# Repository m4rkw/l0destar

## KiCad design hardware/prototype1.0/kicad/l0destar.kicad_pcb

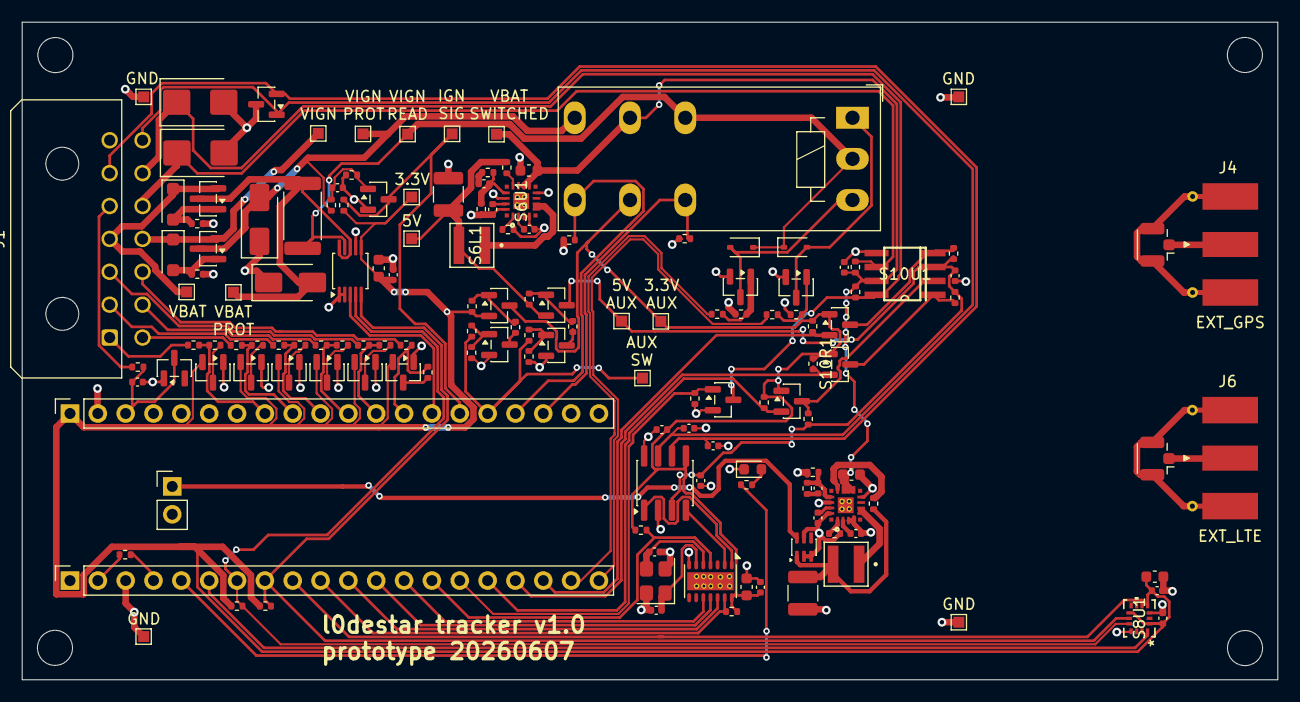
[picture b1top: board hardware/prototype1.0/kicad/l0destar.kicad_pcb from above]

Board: 2 copper layers, 114.5 x 60.0 mm, 153 parts (0 on the bottom side), 101 nets.

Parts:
DS10D2: SMBJ24A; D_SMB
H1, H2, H3, H4: MountingHole; MountingHole_3.2mm_M3
J1: Main connector; Molex_Micro-Fit_3.0_43045-1400_2x07_P3.00mm_Horizontal
J2: Conn_01x20_Socket; PinSocket_1x20_P2.54mm_Vertical
J3: Conn_01x20_Socket_21-40; PinSocket_1x20_P2.54mm_Vertical_21-40
J4: EXT_GPS; SMA_Molex_73251-1153_EdgeMount_Horizontal
J5: INT_GPS; U.FL_Hirose_U.FL-R-SMT-1_Vertical
J6: EXT_LTE; SMA_Molex_73251-1153_EdgeMount_Horizontal
J7: INT_LTE; U.FL_Hirose_U.FL-R-SMT-1_Vertical
J8: Conn_01x02_Pin; PinHeader_1x02_P2.54mm_Vertical
S1C1, S3C2, S4C1, S8C1, S8C3, S9C1, S9C2, S9C5, S10C1, S10C2: 100nF; C_0402_1005Metric
S1D1: BZX84C3V3; SOT-23
S1R1, S13R1: 1K; R_0402_1005Metric
S1R2, S1R3: 4.7K; R_0402_1005Metric
S1R4, S4R2, S5R1, S5R4, S6R4, S6R8, S7R2, S7R4, S7R6, S7R8, S11R1, S11R3, S11R5, S11R7, S11R9, S11R11: 100K; R_0402_1005Metric
S2D1, S2D3: BZT52C15; D_SOD-123F
S2D2, S2D4: SMAJ24A; D_SMA
S2Q1, S2Q2, S7Q2, S7Q4: SI2301CDS-T1-GE3; SOT-23
S2R1, S2R2, S5R2, S5R3, S5R5, S5R6, S7R1, S7R3, S7R5, S7R7, S9R1, S9R2, S10R1, S10R2, S10R3, S10R4, S10R5, S10R6, S10R9, S11R2, S11R4, S11R6, S11R8, S11R10, S11R12: 10K; R_0402_1005Metric
S3C1: 1uF; C_0603_1608Metric
S3R1: 15m (CSS2H-2512R-L150F); R_2512_6332Metric
S3U1: INA228; TSSOP-10_3x3mm_P0.5mm
S4Q1, S5Q1, S5Q2, S7Q1, S7Q3: AO3400A; SOT-23
S4R1, S4R3: 56K; R_0402_1005Metric
S5D1, S5D2: 1N4148WS; D_SOD-323
S5K1: RT424F12; Relay_DPDT_Schrack-RT2-FormC-Dual-Coil_RM5mm
S6C1, S6C6: 4.7uF; C_0603_1608Metric
S6C2, S6C7: 10nF; C_0402_1005Metric
S6C3, S6C8: 1uF; C_0402_1005Metric
S6C4, S6C9: 10pF; C_0402_1005Metric
S6C5, S6C10: 22uF (X7R 1206); C_1210_3225Metric
S6L1, S6L2: XFL4020-222ME; IND_XFL4020-222ME
S6R1, S6R5: 18.2K; R_0402_1005Metric
S6R2: 187K; R_0402_1005Metric
S6R3, S6R7: 1M; R_0402_1005Metric
S6R6: 228K; R_0402_1005Metric
S6U1, S6U3: LT8609SIV_PBF; REG_LT8609SIV_PBF_WITH_VIAS
S6U4: LM66100DCK; SOT-363_SC-70-6
S8C2, S9C6: 10uF; C_0603_1608Metric
S8U1: ASM330LHHXG1TR; LGA14_2P5X3_STM
S9C3, S9C4: 4.7nF; C_0402_1005Metric
S9C7, S9C8: 12pF; C_0402_1005Metric
S9D1: NUP2105L; SOT-23
S9U1: TJA1051T-3; SOIC-8_3.9x4.9mm_P1.27mm
S9U2: MCP2518FD-xQBB; MCP2518FD-xQBB_WITH_VIAS
S9Y1: Lucki L327S400H11L; Crystal_SMD_3225-4Pin_3.2x2.5mm
S10D1: SMBJ24A; D_SMB
S10Q1, S10Q2, S10Q3: BSS138; SOT-23
S10Q4: 2N7002; SOT-23
S10R7, S10R8: 510R; R_0402_1005Metric
S10U1: L9637D; SO08
S11D1, S11D2, S11D3, S11D4, S11D5, S11D6: BAT54S; SOT-23
S13D1: LED; LED_0603_1608Metric
TP1, TP2, TP3, TP4, TP5, TP6, TP7, TP8, TP9, TP10, TP11, TP12, TP13, TP14, TP15, TP16: TestPoint; TestPoint_Pad_1.0x1.0mm

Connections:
+3.3V: J3.40 (Pin_1), S1R2.2, S1R3.2, S3C1.2, S3C2.2, S3U1.6 (VS), S4R3.1, S7Q4.2, S7R8.1, S8C1.2, S8C2.2, S8C3.2, S8U1.5 (VDD_IO), S8U1.8 (VDD), S8U1.12 (CS), S11D1.2 (K), S11D2.2 (K), S11D3.2 (K), S11D4.2 (K), S11D5.2 (K), S11D6.2 (K), TP8.1 (1_1)
+3.3V_AUX: S5K1.21, S7Q4.3, S9C1.1, S9C5.1, S9C6.1, S9R1.1, S9R2.1, S9U1.5 (VIO), S9U2.14 (VDD), S10Q1.1 (G), S10Q2.1 (G), S10Q3.1 (G), S10R1.1, S10R3.1, S10R5.1, TP11.1 (1_1)
+4.2V: J8.1, S6U4.6 (VOUT)
+5V: S6C5.1, S6L1.2, S6R4.1, S7Q2.2, S7R4.1, TP10.1 (1_1)
+5V_AUX: S7Q2.3, S9C2.1, S9U1.3 (VCC), S10C2.2, S10R2.1, S10R4.1, S10R6.1, S10U1.3 (VCC), TP13.1 (1_1)
ACCELL_INT1: J2.6, S8U1.4 (INT1)
ACCELL_INT2: J2.9, S8U1.9 (INT2)
AIO1: J1.1, S11R1.1
AIO2: J1.8, S11R3.1
AIO3: J1.2, S11R5.1
AIO4: J1.9, S11R7.1
AIO5: J1.3, S11R9.1
AIO6: J1.10, S11R11.1
AUX_SW: J3.25 (Pin_16), S7R1.1, S7R5.1, TP7.1 (1_1)
CAN_CS: J2.10, S9R1.2, S9U2.13 (~CS)
CAN_H: J1.14, S9C3.1, S9D1.1 (K), S9U1.7 (CANH)
CAN_INT: J2.14, S9R2.2, S9U2.4 (~INT)
CAN_L: J1.6, S9C4.1, S9D1.2 (K), S9U1.6 (CANL)
CAN_SCK: J2.13, S9U2.10 (SCK)
CAN_SDI: J2.12, S9U2.11 (SDI)
CAN_SDO: J2.11, S9U2.12 (SDO)
GND: DS10D2.2 (A2), J1.7, J2.3 (GND), J3.39 (Pin_2), J8.2, S1C1.1, S1D1.1 (A), S2D2.1 (A1), S2D4.1 (A1), S2R1.2, S2R2.2, S3C1.1, S3C2.1, S3U1.1 (A1), S3U1.2 (A0), S3U1.7 (GND), S4C1.2, S4Q1.2 (S), S4R2.1, S5Q1.2 (S), S5Q2.2 (S), S5R1.1, S5R4.2, S5R5.2, S5R6.2, S6C1.2, S6C2.2, S6C3.2, S6C5.2, S6C6.2, S6C7.2, S6C8.2, S6C10.2, S6R1.2, S6R2.2, S6R5.2, S6R6.2, S6U1.3 (GND), S6U1.4 (GND), S6U1.8 (GND), S6U1.14 (GND), S6U1.16 (SYNC), S6U1.17 (GND), S6U3.3 (GND), S6U3.4 (GND), S6U3.8 (GND), S6U3.14 (GND), S6U3.16 (SYNC), S6U3.17 (GND), S6U4.2 (GND), S6U4.3 (~CE), S6U4.5 (ST), S7Q1.2 (S), S7Q3.2 (S), S7R2.1, S7R6.1, S8C1.1, S8C2.1, S8C3.1, S8U1.1 (SDO/SA0), S8U1.7 (GND), S9C1.2, S9C2.2, S9C3.2, S9C4.2, S9C5.2, S9C6.2, S9C7.2, S9C8.2, S9D1.3 (A), S9U1.2 (GND), S9U1.8 (S), S9U2.7 (VSS), S9U2.15 (VSS), S9Y1.2 (G), S9Y1.4 (G), S10C1.1, S10C2.1, S10D1.2 (A2), S10Q4.2 (S), S10R9.2, S10U1.5 (GND), S11D1.1 (A), S11D2.1 (A), S11D3.1 (A), S11D4.1 (A), S11D5.1 (A), S11D6.1 (A), S13D1.1 (K), TP12.1 (1_1), TP14.1 (1_1), TP15.1 (1_1), TP16.1 (1_1)
GPIO1: J3.33 (Pin_8), S11R1.2, S11R2.2
GPIO2: J3.32 (Pin_9), S11R3.2, S11R4.2
GPIO3: J3.31 (Pin_10), S11R5.2, S11R6.2
GPIO4: J3.30 (Pin_11), S11R7.2, S11R8.2
GPIO5: J3.29 (Pin_12), S11R9.2, S11R10.2
GPIO6: J3.28 (Pin_13), S11R11.2, S11R12.2
I2C_SCL: J2.8, S1R3.1, S3U1.5 (SCL), S8U1.13 (SCL)
I2C_SDA: J2.7, S1R2.1, S3U1.4 (SDA), S8U1.14 (SDA)
IGN_SENSE: J3.26 (Pin_15), S4Q1.3 (D), S4R3.2, TP6.1 (1_1)
ISO9141_K: J1.12, S10D1.1 (A1), S10R7.2, S10U1.6 (K)
ISO9141_L: DS10D2.1 (A1), J1.13, S10Q4.3 (D), S10R8.2, S10U1.8 (LI)
K_RX: J2.17, S10Q1.2 (S), S10R1.2
K_TX: J2.18, S10Q2.2 (S), S10R3.2
L_RECV: J2.16, S10Q3.2 (S), S10R5.2
L_SEND: J2.15, S10Q4.1 (G), S10R9.1
unnamed: J2.4 (ENABLE), S1R4.2
unnamed: J4.2 (Ext), J5.2 (Ext)
unnamed: J4.1 (In), J5.1 (In)
unnamed: J6.2 (Ext), J7.2 (Ext)
unnamed: J6.1 (In), J7.1 (In)
unnamed: S2D1.2 (A), S2Q1.1, S2R1.1
unnamed: S2D3.2 (A), S2Q2.1, S2R2.1
unnamed: S4C1.1, S4Q1.1 (G), S4R1.2, S4R2.2
unnamed: S5D1.2 (A), S5K1.A1, S5Q1.3 (D)
unnamed: S5D2.2 (A), S5K1.A2, S5Q2.3 (D)
unnamed: S5Q1.1 (G), S5R1.2, S5R2.2
unnamed: S5Q2.1 (G), S5R3.2, S5R4.1
unnamed: S6C4.2, S6R3.2
unnamed: S6C9.2, S6R7.2
unnamed: S6L1.1, S6U1.5 (SW), S6U1.6 (SW)
unnamed: S6L2.1, S6U3.5 (SW), S6U3.6 (SW)
unnamed: S6C4.1, S6R2.1, S6R3.1, S6U1.13 (FB)
unnamed: S6C3.1, S6U1.2 (INTVCC)
unnamed: S6U1.7 (N/C), S6U1.NC1 (N/C), S6U1.NC2 (N/C), S6U1.NC3 (N/C), S6U1.NC4 (N/C)
unnamed: S6R4.2, S6U1.12 (PG)
unnamed: S6R1.1, S6U1.1 (RT)
unnamed: S6C2.1, S6U1.15 (TR/SS)
unnamed: S6C9.1, S6R6.1, S6R7.1, S6U3.13 (FB)
unnamed: S6C8.1, S6U3.2 (INTVCC)
unnamed: S6U3.7 (N/C), S6U3.NC1 (N/C), S6U3.NC2 (N/C), S6U3.NC3 (N/C), S6U3.NC4 (N/C)
unnamed: S6R8.2, S6U3.12 (PG)
unnamed: S6R5.1, S6U3.1 (RT)
unnamed: S6C7.1, S6U3.15 (TR/SS)
unnamed: S6C10.1, S6L2.2, S6R8.1, S6U4.1 (VIN)
unnamed: S7Q1.3 (D), S7R3.2
unnamed: S7Q1.1 (G), S7R1.2, S7R2.2
unnamed: S7Q2.1, S7R3.1, S7R4.2
unnamed: S7Q3.3 (D), S7R7.2
unnamed: S7Q3.1 (G), S7R5.2, S7R6.2
unnamed: S7Q4.1, S7R7.1, S7R8.2
unnamed: S9U1.4 (RXD), S9U2.2 (RXCAN)
unnamed: S9U1.1 (TXD), S9U2.1 (TXCAN)
unnamed: S9C8.1, S9U2.6 (OSC1), S9Y1.1
unnamed: S9C7.1, S9U2.5 (OSC2), S9Y1.3
unnamed: S10Q1.3 (D), S10R2.2, S10U1.1 (RX)
unnamed: S10Q2.3 (D), S10R4.2, S10U1.4 (TX)
unnamed: S10Q3.3 (D), S10R6.2, S10U1.2 (LO)
unnamed: S11D1.3 (COM), S11R2.1
unnamed: S11D2.3 (COM), S11R4.1
unnamed: S11D3.3 (COM), S11R6.1
unnamed: S11D4.3 (COM), S11R8.1
unnamed: S11D5.3 (COM), S11R10.1
unnamed: S11D6.3 (COM), S11R12.1
unnamed: S13D1.2 (A), S13R1.2
RESET: J1.5, S1R1.1
RESET_SIGNAL: J3.38 (Pin_3), S1C1.2, S1D1.3 (K), S1R1.2
RLY_RST: J2.19, S5R3.1
RLY_RST_FB: J3.24 (Pin_17), S5K1.24, S5R5.1
RLY_SET: J2.20, S5R2.1
RLY_SET_FB: J3.23 (Pin_18), S5K1.22, S5R6.1
STATUS: J2.5 (P9), S13R1.1
VBAT: J1.4, S2D3.1 (K), S2Q2.2, TP1.1 (1_1)
VBAT_ALRT: J3.27 (Pin_14), S3U1.3 (~Alert)
VBAT_PROT: S2D4.2 (A2), S2Q2.3, S3R1.1, S3U1.8 (Vbus), S3U1.10 (Vin+), TP3.1 (1_1)
VBAT_PROT_READ: S3R1.2, S3U1.9 (Vin-), S5D1.1 (K), S5D2.1 (K), S5K1.12, S5K1.A3, TP5.1 (1_1)
VBAT_SWITCHED: S5K1.11, S6C1.1, S6C6.1, S6U1.9 (VIN), S6U1.10 (VIN), S6U1.11 (EN/UV), S6U3.9 (VIN), S6U3.10 (VIN), S6U3.11 (EN/UV), S10C1.2, S10R7.1, S10R8.1, S10U1.7 (VS), TP9.1 (1_1)
VIGN: J1.11, S2D1.1 (K), S2Q1.2, TP2.1 (1_1)
VIGN_PROT: S2D2.2 (A2), S2Q1.3, S4R1.1, S5K1.14, TP4.1 (1_1)
VSYS: J2.2 (VSYS), S1R4.1

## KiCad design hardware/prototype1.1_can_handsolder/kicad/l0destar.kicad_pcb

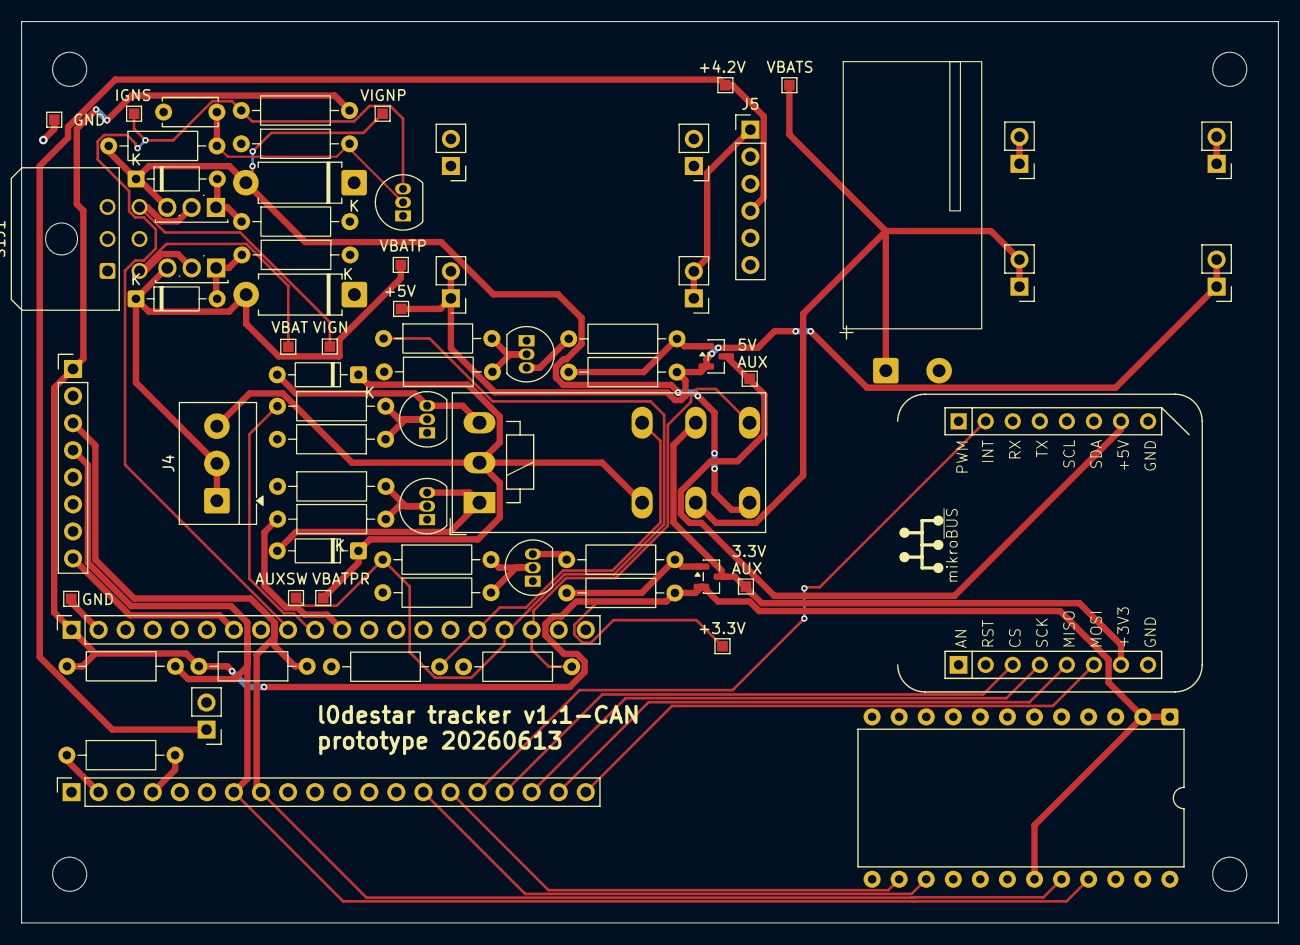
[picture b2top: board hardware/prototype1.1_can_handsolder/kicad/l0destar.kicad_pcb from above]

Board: 2 copper layers, 118.0 x 84.6 mm, 76 parts (0 on the bottom side), 44 nets.

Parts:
CON1: MIKROBUS_HOST_CONN
H1, H2, H3, H4: MountingHole; MountingHole_3.2mm_M3
J1: VCC; PinHeader_1x02_P2.54mm_Vertical
J2: Conn_01x20_Socket; MakerDiary_nRF9151_ConnectKit_PinHeader_1-20
J3: Conn_01x20_Socket_21-40; MakerDiary_nRF9151_ConnectKit_PinHeader_21-40
J4: Conn_01x03_Pin; TerminalBlock_4Ucon_1x03_P3.50mm_Horizontal
J5: LM66200; LM66200_Ideal_Diode_Breakout
S1J1: Main connector; Molex_Micro-Fit_3.0_43045-0600_2x03_P3.00mm_Horizontal
S1R1, S1R2: 4.7K; R_Axial_DIN0207_L6.3mm_D2.5mm_P10.16mm_Horizontal
S1R3, S4R2, S5R1, S5R4, S7R2, S7R4, S7R6, S7R8: 100K; R_Axial_DIN0207_L6.3mm_D2.5mm_P10.16mm_Horizontal
S2D1, S2D3: BZX79-C15; D_DO-35_SOD27_P7.62mm_Horizontal
S2D2, S2D4: P6KE24CA; D_DO-15_P10.16mm_Horizontal
S2Q1, S2Q2: FQU11P06; TO-251-3_Vertical
S2R1, S2R2, S5R2, S5R3, S5R5, S5R6, S7R1, S7R3, S7R5, S7R7: 10K; R_Axial_DIN0207_L6.3mm_D2.5mm_P10.16mm_Horizontal
S3J1: INA228; PinHeader_1x08_P2.54mm_Vertical
S4C1: 100nF; C_Disc_D5.0mm_W2.5mm_P5.00mm
S4R1, S4R3: 56K; R_Axial_DIN0207_L6.3mm_D2.5mm_P10.16mm_Horizontal
S5D1, S5D2: 1N4148; D_DO-35_SOD27_P7.62mm_Horizontal
S5K1: RT424F12; Relay_DPDT_Schrack-RT2-FormC-Dual-Coil_RM5mm
S5Q1, S5Q2, S5Q3, S7Q1, S7Q3: ZVN4206A; TO-92_Inline
S6C1: 2200uF; CP_Radial_D12.5mm_P5.00mm_Horizontal_L25mm
S6U1_J1, S6U1_J5: BUCK INPUT +; PinHeader_1x02_P2.54mm_Vertical
S6U1_J2, S6U1_J6: BUCK INPUT -; PinHeader_1x02_P2.54mm_Vertical
S6U1_J3, S6U1_J7: BUCK OUTPUT +; PinHeader_1x02_P2.54mm_Vertical
S6U1_J4, S6U1_J8: BUCK OUTPUT -; PinHeader_1x02_P2.54mm_Vertical
S7Q2, S7Q4: DMG3415U; SOT-23
S8U1: ASM330LHHXG1TR; DIP-24_W15.24mm
TP1, TP2, TP3, TP4, TP5, TP6, TP7, TP8, TP9, TP10, TP11, TP12, TP13, TP14, TP15: TestPoint; TestPoint_Pad_1.0x1.0mm

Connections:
+3.3V: J3.40 (Pin_1), S1R1.2, S1R2.2, S3J1.1, S4R3.1, S7Q4.2 (S), S7R8.1, S8U1.1, S8U1.2, S8U1.19, TP8.1 (1_1)
+3.3V_AUX: CON1.P7 (3V3), S5K1.21, S7Q4.3 (D), TP11.1 (1_1)
+4.2V: J1.1, J5.4, TP15.1 (1_1)
+5V: S6U1_J3.1, S6U1_J3.2, S6U1_J5.1, S6U1_J5.2, S7Q2.2 (S), S7R4.1, TP10.1 (1_1)
+5V_AUX: CON1.P10 (5V), S7Q2.3 (D), TP13.1 (1_1)
ACCELL_INT1: J2.15, S8U1.14
ACCELL_INT2: J2.14, S8U1.15
AUX_SW: J3.24 (Pin_17), S7R1.1, S7R5.1, TP7.1 (1_1)
CAN_CS: CON1.P3 (CS), J2.17
CAN_INT: CON1.P15 (INT), J2.16
CAN_MISO: CON1.P5 (MISO), J2.19
CAN_MOSI: CON1.P6 (MOSI), J2.20
CAN_SCK: CON1.P4 (SCK), J2.18
GND: CON1.P8 (GND1), CON1.P9 (GND2), J1.2, J2.3 (GND), J3.39 (Pin_2), J5.3, S1J1.3, S2D2.1 (A1), S2D4.1 (A1), S2R1.2, S2R2.2, S3J1.2, S4C1.2, S4R2.1, S5Q1.1 (S), S5Q2.1 (S), S5Q3.1 (S), S5R1.1, S5R4.2, S5R5.2, S5R6.2, S6C1.2, S6U1_J2.1, S6U1_J2.2, S6U1_J4.1, S6U1_J4.2, S6U1_J6.1, S6U1_J6.2, S6U1_J8.1, S6U1_J8.2, S7Q1.1 (S), S7Q3.1 (S), S7R2.1, S7R6.1, S8U1.13, S8U1.22, TP12.1 (1_1), TP14.1 (1_1)
I2C_SCL: J2.8, S1R2.1, S3J1.3, S8U1.20
I2C_SDA: J2.7, S1R1.1, S3J1.4, S8U1.21
IGN_SENSE: J3.32 (Pin_9), S4R3.2, S5Q3.3 (D), TP6.1 (1_1)
unnamed: J2.4 (ENABLE), S1R3.2
unnamed: J5.1, S6U1_J7.1, S6U1_J7.2
unnamed: S2D1.2 (A), S2Q1.1 (G), S2R1.1
unnamed: S2D3.2 (A), S2Q2.1 (G), S2R2.1
unnamed: S5D1.2 (A), S5K1.A1, S5Q1.3 (D)
unnamed: S5D2.2 (A), S5K1.A2, S5Q2.3 (D)
unnamed: S5Q1.2 (G), S5R1.2, S5R2.2
unnamed: S5Q2.2 (G), S5R3.2, S5R4.1
unnamed: S4C1.1, S4R1.2, S4R2.2, S5Q3.2 (G)
unnamed: S7Q1.3 (D), S7R3.2
unnamed: S7Q1.2 (G), S7R1.2, S7R2.2
unnamed: S7Q2.1 (G), S7R3.1, S7R4.2
unnamed: S7Q3.3 (D), S7R7.2
unnamed: S7Q3.2 (G), S7R5.2, S7R6.2
unnamed: S7Q4.1 (G), S7R7.1, S7R8.2
RLY_RST: J3.31 (Pin_10), S5R3.1
RLY_RST_FB: J3.23 (Pin_18), S5K1.24, S5R5.1
RLY_SET: J3.30 (Pin_11), S5R2.1
RLY_SET_FB: J3.25 (Pin_16), S5K1.22, S5R6.1
VBAT: S1J1.4, S2Q2.2 (D), TP1.1 (1_1)
VBAT_ALRT: J3.34 (Pin_7), S3J1.8
VBAT_PROT: J4.1, J4.2, S2D3.1 (K), S2D4.2 (A2), S2Q2.3 (S), TP3.1 (1_1)
VBAT_PROT_READ: J4.3, S5D1.1 (K), S5D2.1 (K), S5K1.12, S5K1.A3, TP5.1 (1_1)
VBAT_SWITCHED: S5K1.11, S6C1.1, S6U1_J1.1, S6U1_J1.2, TP9.1 (1_1)
VIGN: S1J1.6, S2Q1.2 (D), TP2.1 (1_1)
VIGN_PROT: S2D1.1 (K), S2D2.2 (A2), S2Q1.3 (S), S4R1.1, S5K1.14, TP4.1 (1_1)
VSYS: J2.2 (VSYS), S1R3.1

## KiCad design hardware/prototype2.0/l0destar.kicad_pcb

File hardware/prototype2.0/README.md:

# l0destar v2.0 prototype

## Overview

NOTE: THIS HAS NOT BEEN TESTED, USE AT YOUR OWN RISK

This is a prototype l0destar vehicle tracker PCB designed to be hand-solderable.
It makes use of the [Makerdiary nRF9151 Connect Kit](https://makerdiary.com/products/nrf9151-connectkit) to provide the LTE and GPS
functions.

Features:

 - 12V live and 12V ignition inputs with TVS and reverse polarity protection
 - Ignition presence sensing
 - Programmatic relay switching to switch the power supply between 12V live and
   12V ignition
 - INA228 voltage reading
 - CAN interface
 - ISO-9141 interface
 - Dual buck converters with high efficiency
 - Auxillary 3.3V, 5V and 12V power rails that can be turned off to save power
 - ASM330LHHXG1TR 6-axis IMU gyro/accelerometer
 - 2200uF bulk cap on the 12V supply to keep it alive during turnover
 - Six general-purpose digital AIO pins capable of handling 0-30V

## Power supply

The Connect Kit can be powered through VBUS which would be much simpler as it
can take 5V, but then you have to disconnect the power before connecting a USB
cable. Same for the Nordic dev board - they both explicitly say not to connect
powered USB and VBUS at the same time. Because the intention is to install this
in a vehicle for testing the pragmatic decision was taken to power it with a
4.2V buck feeding the battery connector. With this power connection we can
connect USB-C at any time to update the firmware without needing to disconnect
power.

## Parts list

| Part | Description | Quantity |
|------|-------------|----------|
| [Makerdiary nRF9151 Connect Kit](https://makerdiary.com/products/nrf9151-connectkit) | MCU and GSM/GPS | 1 |
| [Molex 43045-1400](https://uk.farnell.com/molex/43045-1400/conn-r-a-pcb-hdr-14pos-2row-3mm/dp/9732985) | Main connector | 1 |
| [20-pin pcb header](https://amzn.to/44hTFGN) | Makerdiary board connector | 2 |
| [U.FL-R-SMT(01) RF COAXIAL, U.FL, STRAIGHT JACK, 50O](https://uk.farnell.com/3908021) | u.FL connectors | 2 |
| [SMA-J-P-H-RA-TH1 RF COAXIAL, SMA JACK, 50 OHM](https://uk.farnell.com/2856817) | through-hole SMA connectors | 2 |
| [3521510RFT RES, 510R, 1%, 2W, 2512](https://uk.farnell.com/2117495) | >= 1W K-line pullup resistor | 1 |
| 0805 1K resistor | 1% 0805 | 3 |
| 0805 4.7K resistor | 1% 0805 | 2 |
| 0805 10K resistor | 1% 0805 | 20 |
| 0805 18.2K resistor | 1% 0805 | 2 |
| 0805 56K resistor | 1% 0805 | 2 |
| 0805 100K resistor | 1% 0805 | 15 |
| 0805 187K resistor | 1% 0805 | 1 |
| 0805 226K resistor | 1% 0805 | 1 |
| 0805 1M resistor | 1% 0805 | 2 |
| [MCLRP12JTWSR050 CURRENT SENSE RES](https://uk.farnell.com/2828382) | 15Mohm current-sensing resistor | 1 |
| 0805 10pF | 0603 10pF ceramic cap | 2 |
| 0603 27pF | 0603 27pF ceramic cap | 2 |
| 0603 100pF | 0603 100pF ceramic cap | 2 |
| 0805 4.7nF | 0805 4.7nF ceramic cap | 2 |
| 0603 10nF | 0603 10nF ceramic cap | 1 |
| 0805 100nF | 0805 100nF ceramic cap | 9 |
| 0805 1uF | 0805 1uF ceramic cap | 4 |
| 0805 4.7uF | 0805 4.7uF ceramic cap | 2 |
| 0805 10uF | 0805 10uF ceramic cap | 2 |
| 0805 22uF | 0805 22uF ceramic cap | 2 |
| 220uF | 220uF SMD capacitor | 1 |
| [EEEFK1E222AM 2200uF SMD 25V capacitor](https://uk.farnell.com/panasonic/eeefk1e222am/cap-2200-f-25v-radial-smd/dp/2326204) 2200uF | 1 |
| 0603 LED | 0603 status LED | 3 |
| 1N4148W | 1N4148W diode | 2 |
| SMBJ30A | SMBJ30A TVS diode | 6 |
| BZX84C15 | BZX84C15 zener diode | 2 |
| BAT54S | BAT54S shottky diode | 6 |
| A03407A | A03407A P-channel MOSFET | 2 |
| 2N7002 | 2N7002 N-channel MOSFET | 6 |
| DMG3415U | DMG3415U P-channel MOSFET | 2 |
| [ABM8G-40.000MHZ-18-D2Y-T](https://uk.farnell.com/abracon/abm8g-40-000mhz-18-d2y-t/crystal-40mhz-18pf-3-2mm-x-2-5mm/dp/3819752)
| 40MHz crystal (CAN interface) | 1 |
| [XFL4020-222ME](https://uk.farnell.com/coilcraft/xfl4020-222mec/inductor-2-2uh-8a-20-pwr-38mhz/dp/2289216) | Power inductor, buck converter | 2 |
| [0603HP-68NXGLU](https://uk.farnell.com/coilcraft/0603hp-68nxglu/inductor-68nh-2-2ghz-rf-smd/dp/2286163) | Wirewound inductor, antenna, 47-100 nH, SRF > 2 GHz | 1 |
| [BLM18KG601SN1D](https://uk.farnell.com/murata/blm18kg601sn1d/ferrite-bead-0603-600r-1-3a/dp/1781094) | Ferrite bead 600R | 1 |
| [INA228](https://www.aliexpress.com/item/1005005873662957.html) | INA228, voltage reading | 1 |
| [RT424F12](https://uk.farnell.com/schrack-te-connectivity/rt424f12/relay-dpdt-250vac-8a/dp/1175085) | 12V bistable relay | 1 |
| [LM66100](https://www.aliexpress.com/item/1005008565117953.html) | LM66100, ideal diode | 9 |
| [LT8609AIMSE](https://www.aliexpress.com/item/1005008917068578.html) | LT8609, buck converter | 2 |
| [STEVAL-MKI212V1](https://www.st.com/en/evaluation-tools/steval-mki212v1.html) | ASM330LHHX accelerometer breakout module | 1 |
| [TJA1051T-3](https://uk.farnell.com/nxp/tja1051t-3-1j/can-fd-transceiver-5mbps-soic/dp/2574963) | TJA1051T-3, CAN interface | 1 |
| [NUP2105L](https://uk.farnell.com/diotec/nup2105l/tvs-diode-bidir-44v-sot-23-350w/dp/4574509) | NUP2105L, CAN protector | 1 |
| [MCP2518FD](https://uk.farnell.com/microchip/mcp2518fdt-e-sl/can-controller-aec-q100-40to125deg/dp/3796956) | MCP2518FD, CAN FD controller | 1 |
| [TXS0104ED](https://uk.farnell.com/texas-instruments/txs0104edr/volt-level-translator-4-bit-soic/dp/3120986) | TXS0104ED, level shifter | 1 |
| [L9637D](https://uk.farnell.com/stmicroelectronics/e-l9637d/monolithic-bus-driver-40-to-150deg/dp/3129892) | L9637D ISO-9141 K-line interface | 1 |

## Notes

- If you don't care about CAN the CAN components and crystal can be omited
- If you don't care about the K-line / ISO-9141 interface the chip for it can be omited
- The breakouts can either be soldered directly or mounted on PCB pin headers, I
  would suggest the latter for ease of re-use
- Never plug or unplug anything into the Nordic dev board while anything is
  powered (I killed at least one dev board this way)
- This PCB has not been tested or validated at all yet, I would strongly
  recommend carefully testing it (ideally with an oscilloscope) before
  connecting it to the dev board

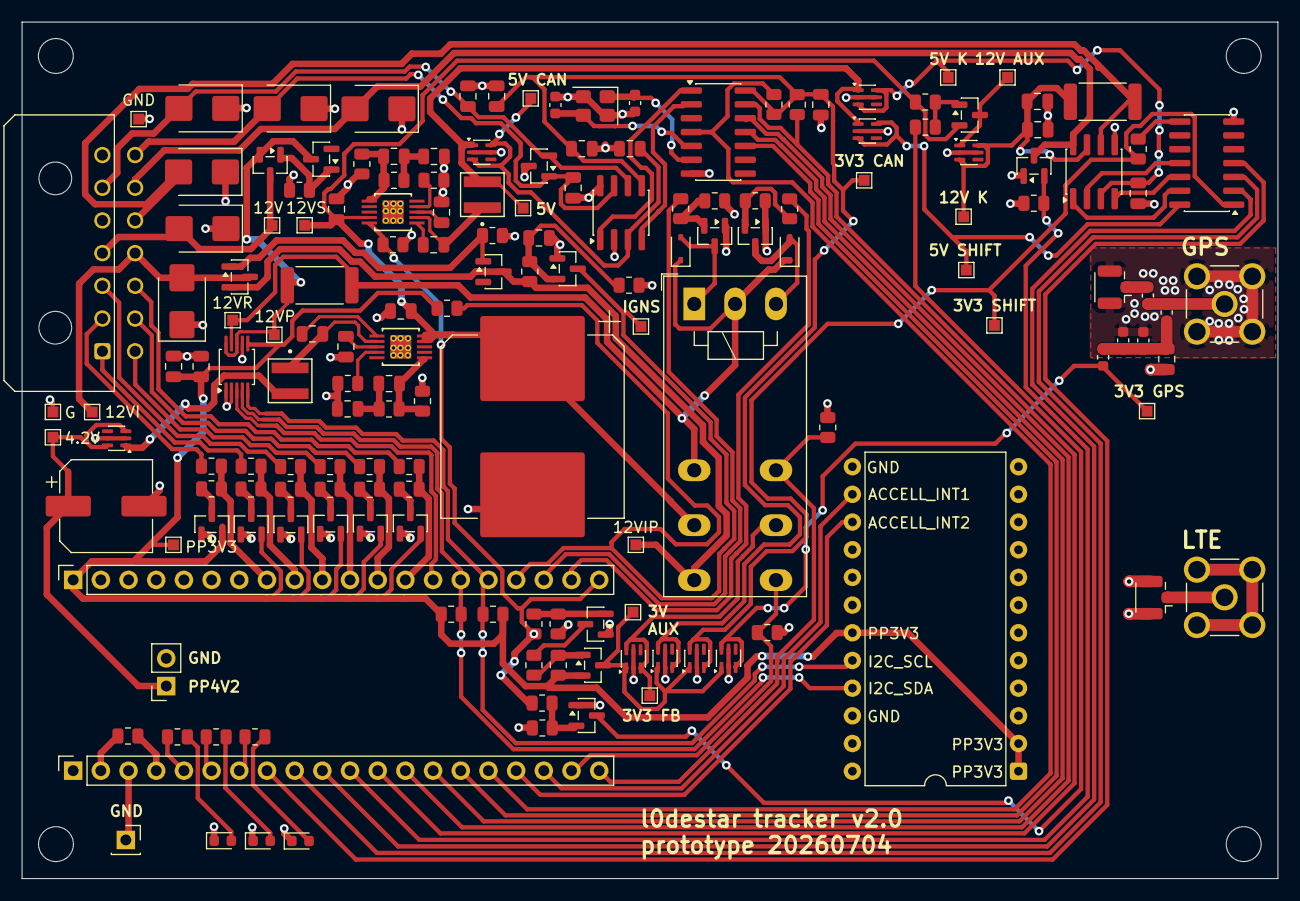
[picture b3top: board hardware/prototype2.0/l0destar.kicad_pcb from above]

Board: 2 copper layers, 115.2 x 78.6 mm, 168 parts (0 on the bottom side), 108 nets.

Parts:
C1: 2200uF; CP_Elec_16x17.5
C2: 220uF; CP_Elec_8x6.9
GND1, GND2: TestPoint; TestPoint_Pad_1.0x1.0mm
GND3: TestPoint; PinSocket_1x01_P2.54mm_Vertical
H1, H2, H3, H4: MountingHole; MountingHole_3.2mm_M3
IGN_SENSE1: TestPoint; TestPoint_Pad_1.0x1.0mm
PP3V3, PP3V3_AUX1, PP3V3_CAN1, PP3V3_GPS1, PP3V3_RLY_FB1, PP3V3_SHIFT1, PP4V2, PP5VK1, PP5V_AUX1, PP5V_CAN1, PP5V_SHIFT1, PP12V1, PP12VI1, PP12VIP1, PP12VK1, PP12VP1, PP12VR1, PP12VS1, PP12V_AUX1: TestPoint; TestPoint_Pad_1.0x1.0mm
S1D1, S1D2, S1D3: LED; LED_0603_1608Metric
S1J1: Main connector; Molex_Micro-Fit_3.0_43045-1400_2x07_P3.00mm_Horizontal
S1J2: Conn_01x20_Socket; MakerDiary_nRF9151_ConnectKit_PinHeader_1-20
S1J3: Conn_01x20_Socket_21-40; MakerDiary_nRF9151_ConnectKit_PinHeader_21-40
S1J4: VCC; PinSocket_1x02_P2.54mm_Vertical
S1R1, S1R2: 4.7K; R_0805_2012Metric
S1R3, S4R2, S5R1, S5R4, S6R9, S7R6, S7R8, S7R10, S7R12, S11R1, S11R3, S11R5, S11R7, S11R9, S11R11: 100K; R_0805_2012Metric
S1R4, S1R5, S1R6: 1K; R_0805_2012Metric
S2D1, S2D3: BZX84C15; SOT-23
S2D2, S2D4, S9D2, S9D3, S10D1, S10D2: SMBJ30A; D_SMB
S2Q1, S2Q2: AO3407A; SOT-23
S2R1, S2R2, S5R2, S5R3, S5R5, S5R6, S7R5, S7R7, S7R9, S7R11, S9R1, S9R2, S10R9, S10R10, S11R2, S11R4, S11R6, S11R8, S11R10, S11R12: 10K; R_0805_2012Metric
S3C1, S6C3, S6C7, S15C4: 1uF; C_0805_2012Metric
S3C2, S4C1, S6C2, S6C6, S9C1, S9C2, S9C5, S10C1, S10C2: 100nF; C_0805_2012Metric
S3R1: 15m (CSS2H-2512R-L150F); R_2512_6332Metric
S3U1: INA228; TSSOP-10_3x3mm_P0.5mm
S4Q1, S5Q1, S5Q2, S7Q3, S7Q5, S10Q1: 2N7002; SOT-23
S4R1, S4R3: 56K; R_0805_2012Metric
S5D1, S5D2: 1N4148W; D_SOD-323
S5K1: RT424F12; Relay_DPDT_Schrack-RT2-FormC-Dual-Coil_RM5mm
S5U1, S6U3, S9U3, S9U4, S10U3, S10U4, S10U5, S10U6, S15U1: LM66100DCK; SOT-363_SC-70-6
S6C1, S6C8: 4.7uF; C_0805_2012Metric
S6C4, S6C9: 10pF; C_0805_2012Metric
S6C5, S6C10: 22uF; C_0805_2012Metric
S6L1, S6L2: XFL4020-222ME; IND_XFL4020-222ME
S6R1, S6R4: 18.2K; R_0805_2012Metric
S6R2: 187K; R_0805_2012Metric
S6R3, S6R6: 1M; R_0805_2012Metric
S6R5: 226K; R_0805_2012Metric
S6U1, S6U2: LT8609AIMSE_PBF; LT8609AIMSE_WITH_GROUND_VIAS
S7Q4: DMG3415U; SOT-23
S7Q6: DMP3098L; SOT-23
S8U1: ASM330LHHXG1TR; DIP-24_W15.24mm
S9C3, S9C4: 4.7nF; C_0805_2012Metric
S9C6, S10C3: 10uF; C_0805_2012Metric
S9C7, S9C8: 18pF; C_0603_1608Metric
S9D1: NUP2105L; SOT-23
S9U1: TJA1051T-3; SOIC-8_3.9x4.9mm_P1.27mm
S9U2: MCP2518FD-xQBB; SOIC-14_3.9x8.7mm_P1.27mm
S9Y1: ABM8G-40.000MHZ-18-D2Y-T; Crystal_SMD_3225-4Pin_3.2x2.5mm
S10R7: 510R; R_2512_6332Metric
S10U1: L9637D; SOIC-8_3.9x4.9mm_P1.27mm
S10U2: TXS0104ED; SOIC-14_3.9x8.7mm_P1.27mm
S11D1, S11D2, S11D3, S11D4, S11D5, S11D6: BAT54S; SOT-23
S15C1, S15C2: 100pF; C_0603_1608Metric
S15C3: 10nF; C_0603_1608Metric
S15FB1: FerriteBead; L_0603_1608Metric
S15J1: GPS_UFL; U.FL_Hirose_U.FL-R-SMT-1_Vertical
S15J2: GPS_SMA; SAMTEC_SMA-J-P-H-RA-TH1
S15J3: GSM_UFL; U.FL_Hirose_U.FL-R-SMT-1_Vertical
S15J4: GSM_SMA; SAMTEC_SMA-J-P-H-RA-TH1
S15L1: 47-100 nH, SRF > 2 GHz; L_0603_1608Metric

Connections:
ACCELL_INT1: S1J2.18, S8U1.14
ACCELL_INT2: S1J2.17, S8U1.15
AIO1: S1J1.2, S11R1.1
AIO2: S1J1.1, S11R3.1
AIO3: S1J1.3, S11R5.1
AIO4: S1J1.8, S11R7.1
AIO5: S1J1.9, S11R9.1
AIO6: S1J1.10, S11R11.1
AUX_ENABLE: S1J3.21 (Pin_20), S6R9.1, S6U1.10 (EN/UV), S7R5.1, S7R9.1
CAN_CS: S1J2.12, S9R1.2, S9U2.13 (~CS)
CAN_H: S1J1.14, S9C3.1, S9D1.1 (K), S9D3.2 (A2), S9U1.7 (CANH)
CAN_INT: S1J2.16, S9R2.2, S9U2.4 (~INT)
CAN_L: S1J1.6, S9C4.1, S9D1.2 (K), S9D2.2 (A2), S9U1.6 (CANL)
CAN_SCK: S1J2.15, S9U2.10 (SCK)
CAN_SDI: S1J2.14, S9U2.11 (SDI)
CAN_SDO: S1J2.13, S9U2.12 (SDO)
GND: C1.2, C2.2, GND1.1 (1_1), GND2.1 (1_1), GND3.1 (1_1), S1D1.1 (K), S1D2.1 (K), S1D3.1 (K), S1J1.7, S1J2.3 (GND), S1J3.39 (Pin_2), S1J4.2, S2D2.1 (A1), S2D4.1 (A1), S2R1.2, S2R2.2, S3C1.1, S3C2.1, S3U1.1 (A1), S3U1.2 (A0), S3U1.7 (GND), S4C1.2, S4Q1.1 (S), S4R2.1, S5Q1.1 (S), S5Q2.1 (S), S5R1.1, S5R4.2, S5R5.2, S5R6.2, S5U1.2 (GND), S5U1.5 (ST), S6C1.2, S6C3.2, S6C5.2, S6C7.2, S6C8.2, S6C10.2, S6R1.2, S6R2.2, S6R4.2, S6R5.2, S6R9.2, S6U1.11 (GND), S6U2.11 (GND), S6U3.2 (GND), S6U3.5 (ST), S7Q3.1 (S), S7Q5.1 (S), S7R6.1, S7R10.1, S8U1.13, S8U1.22, S9C1.2, S9C2.2, S9C3.2, S9C4.2, S9C5.2, S9C6.2, S9C7.2, S9C8.2, S9D1.3 (A), S9D2.1 (A1), S9D3.1 (A1), S9U1.2 (GND), S9U1.8 (S), S9U2.7 (VSS), S9U3.2 (GND), S9U3.5 (ST), S9U4.2 (GND), S9U4.5 (ST), S9Y1.2 (G), S9Y1.4 (G), S10C1.1, S10C2.1, S10C3.1, S10D1.1 (A1), S10D2.1 (A1), S10Q1.1 (S), S10R9.2, S10U1.5 (GND), S10U2.7 (GND), S10U3.2 (GND), S10U3.5 (ST), S10U4.2 (GND), S10U4.5 (ST), S10U5.2 (GND), S10U5.5 (ST), S10U6.2 (GND), S10U6.5 (ST), S11D1.1 (A), S11D2.1 (A), S11D3.1 (A), S11D4.1 (A), S11D5.1 (A), S11D6.1 (A), S15C2.2, S15C3.2, S15C4.2, S15J1.2 (Ext), S15J2.2, S15J2.3, S15J2.4, S15J2.5, S15J3.2 (Ext), S15J4.2, S15J4.3, S15J4.4, S15J4.5, S15U1.2 (GND), S15U1.5 (ST)
GPIO1: S1J3.33 (Pin_8), S11R1.2, S11R2.2
GPIO2: S1J3.32 (Pin_9), S11R3.2, S11R4.2
GPIO3: S1J3.31 (Pin_10), S11R5.2, S11R6.2
GPIO4: S1J3.30 (Pin_11), S11R7.2, S11R8.2
GPIO5: S1J3.29 (Pin_12), S11R9.2, S11R10.2
GPIO6: S1J3.28 (Pin_13), S11R11.2, S11R12.2
I2C_SCL: S1J3.25 (Pin_16), S1R1.1, S3U1.5 (SCL), S8U1.20
I2C_SDA: S1J3.26 (Pin_15), S1R2.1, S3U1.4 (SDA), S8U1.21
IGN_SENSE: IGN_SENSE1.1 (1_1), S1J3.24 (Pin_17), S4Q1.3 (D), S4R3.2
INA_ALRT: S1J3.27 (Pin_14), S3U1.3 (~Alert)
ISO9141_K: S1J1.12, S10D1.2 (A2), S10R7.2, S10U1.6 (K)
ISO9141_L: S1J1.13, S10D2.2 (A2), S10Q1.3 (D), S10U1.8 (LI)
K_RX: S1J2.10, S10U2.2 (A1)
K_TX: S1J2.9, S10U2.3 (A2)
L_RECV: S1J2.8, S10U2.4 (A3)
L_SEND: S1J2.11, S10Q1.2 (G), S10R9.1
unnamed: S1D1.2 (A), S1R4.1
unnamed: S1D2.2 (A), S1R5.1
unnamed: S1D3.2 (A), S1R6.1
unnamed: S1J2.4 (ENABLE), S1R3.2
unnamed: S1J2.5 (P9), S1R4.2
unnamed: S1J2.6, S1R5.2
unnamed: S1J2.7, S1R6.2
unnamed: S2D1.1 (A), S2Q1.1 (G), S2R1.1
unnamed: S2D3.1 (A), S2Q2.1 (G), S2R2.1
unnamed: S4C1.1, S4Q1.2 (G), S4R1.2, S4R2.2
unnamed: S5D1.2 (A), S5K1.A1, S5Q1.3 (D)
unnamed: S5D2.2 (A), S5K1.A2, S5Q2.3 (D)
unnamed: S5Q1.2 (G), S5R1.2, S5R2.2
unnamed: S5Q2.2 (G), S5R3.2, S5R4.1
unnamed: S6C4.2, S6C5.1, S6R3.2
unnamed: S6C9.2, S6C10.1, S6R6.2
unnamed: S6C2.1, S6U1.1 (BST)
unnamed: S6C4.1, S6R2.1, S6R3.1, S6U1.6 (FB)
unnamed: S6C3.1, S6U1.3 (INTVCC)
unnamed: S6R1.1, S6U1.4 (RT)
unnamed: S6C2.2, S6L1.1, S6U1.2 (SW)
unnamed: S6C6.1, S6U2.1 (BST)
unnamed: S6C9.1, S6R5.1, S6R6.1, S6U2.6 (FB)
unnamed: S6C7.1, S6U2.3 (INTVCC)
unnamed: S6R4.1, S6U2.4 (RT)
unnamed: S6C6.2, S6L2.1, S6U2.2 (SW)
unnamed: S6L2.2, S6U3.1 (VIN)
unnamed: S7Q3.3 (D), S7R7.2
unnamed: S7Q3.2 (G), S7R5.2, S7R6.2
unnamed: S7Q4.1 (G), S7R7.1, S7R8.2
unnamed: S7Q5.3 (D), S7R11.2
unnamed: S7Q5.2 (G), S7R9.2, S7R10.2
unnamed: S7Q6.1 (G), S7R11.1, S7R12.2
unnamed: S9U1.4 (RXD), S9U2.2 (RXCAN)
unnamed: S9U1.1 (TXD), S9U2.1 (TXCAN)
unnamed: S9C8.1, S9U2.6 (OSC1), S9Y1.1
unnamed: S9C7.1, S9U2.5 (OSC2), S9Y1.3
unnamed: S10U1.2 (LO), S10U2.11 (B3)
unnamed: S10U1.1 (RX), S10U2.13 (B1)
unnamed: S10U1.4 (TX), S10U2.12 (B2)
unnamed: S10R10.1, S10U2.8 (OE)
unnamed: S11D1.3 (COM), S11R2.1
unnamed: S11D2.3 (COM), S11R4.1
unnamed: S11D3.3 (COM), S11R6.1
unnamed: S11D4.3 (COM), S11R8.1
unnamed: S11D5.3 (COM), S11R10.1
unnamed: S11D6.3 (COM), S11R12.1
unnamed: S15C1.2, S15J2.1, S15L1.2
unnamed: S15C2.1, S15C3.1, S15C4.1, S15FB1.2, S15L1.1
unnamed: S15C1.1, S15J1.1 (In)
unnamed: S15J3.1 (In), S15J4.1
PP3V3: PP3V3.1 (1_1), S1J3.40 (Pin_1), S1R1.2, S1R2.2, S3C1.2, S3C2.2, S3U1.6 (VS), S4R3.1, S7Q4.2 (S), S7R8.1, S8U1.1, S8U1.2, S8U1.19, S11D1.2 (K), S11D2.2 (K), S11D3.2 (K), S11D4.2 (K), S11D5.2 (K), S11D6.2 (K)
PP3V3_AUX: PP3V3_AUX1.1 (1_1), S5U1.1 (VIN), S7Q4.3 (D), S9U4.1 (VIN), S10U3.1 (VIN), S15U1.1 (VIN)
PP3V3_CAN: PP3V3_CAN1.1 (1_1), S9C1.1, S9C5.1, S9C6.1, S9R1.1, S9R2.1, S9U1.5 (VIO), S9U2.14 (VDD), S9U4.3 (~CE), S9U4.6 (VOUT)
PP3V3_GPS: PP3V3_GPS1.1 (1_1), S15FB1.1, S15U1.3 (~CE), S15U1.6 (VOUT)
PP3V3_RLY_FB: PP3V3_RLY_FB1.1 (1_1), S5K1.21, S5U1.3 (~CE), S5U1.6 (VOUT)
PP3V3_SHIFT: PP3V3_SHIFT1.1 (1_1), S10R10.2, S10U2.1 (V_{CCA}), S10U3.3 (~CE), S10U3.6 (VOUT)
PP4V2: C2.1, PP4V2.1 (1_1), S1J4.1, S6U3.3 (~CE), S6U3.6 (VOUT)
PP5VK: PP5VK1.1 (1_1), S10C2.2, S10U1.3 (VCC), S10U5.3 (~CE), S10U5.6 (VOUT)
PP5V_AUX: PP5V_AUX1.1 (1_1), S6L1.2, S9U3.1 (VIN), S10U4.1 (VIN), S10U5.1 (VIN)
PP5V_CAN: PP5V_CAN1.1 (1_1), S9C2.1, S9U1.3 (VCC), S9U3.3 (~CE), S9U3.6 (VOUT)
PP5V_SHIFT: PP5V_SHIFT1.1 (1_1), S10U2.14 (V_{CCB}), S10U4.3 (~CE), S10U4.6 (VOUT)
PP12V: PP12V1.1 (1_1), S1J1.4, S2D4.2 (A2), S2Q2.3 (D)
PP12VI: PP12VI1.1 (1_1), S1J1.11, S2D2.2 (A2), S2Q1.3 (D)
PP12VIP: PP12VIP1.1 (1_1), S2D1.3 (K), S2Q1.2 (S), S4R1.1, S5K1.14
PP12VK: PP12VK1.1 (1_1), S10C1.2, S10C3.2, S10R7.1, S10U1.7 (VS), S10U6.3 (~CE), S10U6.6 (VOUT)
PP12VP: PP12VP1.1 (1_1), S2D3.3 (K), S2Q2.2 (S), S3R1.1, S3U1.8 (Vbus), S3U1.10 (Vin+)
PP12VR: PP12VR1.1 (1_1), S3R1.2, S3U1.9 (Vin-), S5D1.1 (K), S5D2.1 (K), S5K1.12, S5K1.A3
PP12VS: C1.1, PP12VS1.1 (1_1), S5K1.11, S6C1.1, S6C8.1, S6U1.9 (VIN), S6U2.9 (VIN), S6U2.10 (EN/UV), S7Q6.2 (S), S7R12.1
PP12V_AUX: PP12V_AUX1.1 (1_1), S7Q6.3 (D), S10U6.1 (VIN)
RLY_RST: S1J3.22 (Pin_19), S5R3.1
RLY_RST_FB: S1J2.19, S5K1.24, S5R5.1
RLY_SET: S1J3.23 (Pin_18), S5R2.1
RLY_SET_FB: S1J2.20, S5K1.22, S5R6.1
VSYS: S1J2.2 (VSYS), S1R3.1
